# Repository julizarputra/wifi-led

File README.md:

wifi-led
===
This is a personal project to control a strip of WS2812 LEDs using an ESP8266 connected to a wifi network.
The really neat part of this project is that I wrote a (buggy) routine to fetch the wifi ssid and password *over wifi*

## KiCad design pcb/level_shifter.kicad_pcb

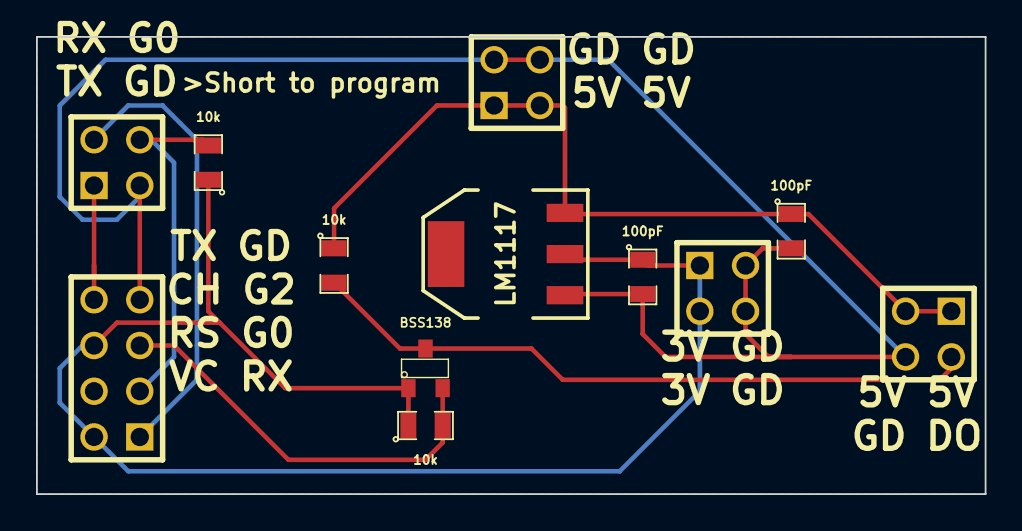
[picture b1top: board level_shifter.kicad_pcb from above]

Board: 2 copper layers, 52.7 x 25.4 mm, 12 parts (0 on the bottom side), 8 nets.

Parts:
3V1, 5V1: CONN_2X2; PIN_ARRAY_2X2
C1, C2: 100pF; SM0805
DBG1: CONN_2X2; PIN_ARRAY_2X2
ESP8266: CONN_4X2; pin_array_4x2
LEDOUT1: CONN_2X2; PIN_ARRAY_2X2
Q1: BSS138; SOT23
R1, R2, R3: 10k; SM0805
U1: LM1117; SOT223

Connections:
+3.3V: 3V1.1, 3V1.3, C2.1, ESP8266.2, ESP8266.6, Q1.1, R1.1, R2.1, U1.2
+5V: 5V1.1, 5V1.3, C1.1, LEDOUT1.1, LEDOUT1.3, R3.1, U1.3
GND: 3V1.2, 3V1.4, 5V1.2, 5V1.4, C1.2, C2.2, DBG1.3, ESP8266.7, LEDOUT1.4, U1.1
unnamed: DBG1.2, ESP8266.1
unnamed: DBG1.4, ESP8266.3, R1.2
unnamed: LEDOUT1.2, Q1.3, R3.2
unnamed: ESP8266.5, Q1.2, R2.2
unnamed: DBG1.1, ESP8266.8

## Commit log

2015-03-26 first
2015-03-26 maybe I just broke everything
2015-03-26 was saving un-initialized variable. Fixed.
2015-03-26 cleanup
2015-05-25 adding client stuff
2015-05-26 working
2015-05-26 cleanup again
2015-05-26 deleted unused include
2015-05-26 added pcb
2015-05-27 fixed led timing
